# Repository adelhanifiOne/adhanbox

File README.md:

# AdhanBox

AdhanBox est un système automatisé de diffusion de l'adhan (appel à la prière) basé sur ESP32.

## Caractéristiques

- 🕌 **Calcul automatique** des horaires de prière basé sur la géolocalisation
- 🔊 **DFPlayer Mini** pour la lecture audio
- 💡 **Bande LED adressable** SK6812/WS2812 (150 LEDs RGB+W)
- 🌐 **Interface Web** de configuration via point d'accès WiFi
- ⏰ **Horloge RTC DS3231** pour le timing précis
- 📍 **Géolocalisation** WiFi (API HERE) ou manuelle

## Séquence de lecture

- **Fajr** : Piste 2 (0002.mp3) + Duaa (0003.mp3)
- **Autres prières** : Piste 1 (0001.mp3) + Duaa (0003.mp3)

## Matériel requis

- ESP32 (240MHz)
- DS3231 RTC avec batterie
- DFPlayer Mini + carte microSD
- Bande LED SK6812/WS2812 (150 LEDs)
- Haut-parleur/amplificateur
- Bouton de configuration

## Brochage

| Composant | Pin ESP32 |
|-----------|-----------|
| LED Data  | GPIO 13   |
| RTC SDA   | GPIO 5    |
| RTC SCL   | GPIO 4    |
| RTC INT   | GPIO 7    |
| DFPlayer RX | GPIO 2  |
| DFPlayer TX | GPIO 1  |
| Bouton Config | GPIO 11 |

## Installation

1. Installer Arduino IDE ou PlatformIO
2. Installer les bibliothèques :
   - RTClib
   - DFRobotDFPlayerMini
   - Preferences (incluse ESP32)
3. Préparer carte SD avec fichiers audio :
   - `0001.mp3` : Adhan standard
   - `0002.mp3` : Adhan Fajr
   - `0003.mp3` : Duaa
4. Téléverser le sketch sur ESP32

## Configuration

1. Au démarrage, l'ESP32 crée un point d'accès WiFi `AdhanBox-XXXX`
2. Se connecter avec smartphone/PC
3. Accéder à l'interface web (redirection automatique)
4. Configurer :
   - Position géographique
   - Fuseau horaire
   - WiFi (optionnel, pour sync NTP)
   - Volume et luminosité

## Interface Web

- **Tableau** : Vue d'ensemble, contrôles rapides
- **Localisation** : Configuration manuelle ou auto (WiFi)
- **Horaires** : Visualisation des heures de prière
- **Avancé** : RTC, LED, diagnostics

## Scènes lumineuses

- Off / Couleurs statiques (Rouge, Rose, Bleu, Violet, Vert, Jaune)
- Dynamic hue : Cycle de couleurs
- Dynamic fade : Transitions douces
- Luminosité réglable 0-100%

## Licence

Tous droits réservés © 2026 Adel Hanifi. Le dépôt est consultable, mais aucune licence n'est accordée : toute reproduction, modification, distribution ou fabrication demande une autorisation écrite. Voir [LICENSE](LICENSE).

## Auteur

Développé pour la communauté musulmane 🤲

---
**Version:** 1.3.0

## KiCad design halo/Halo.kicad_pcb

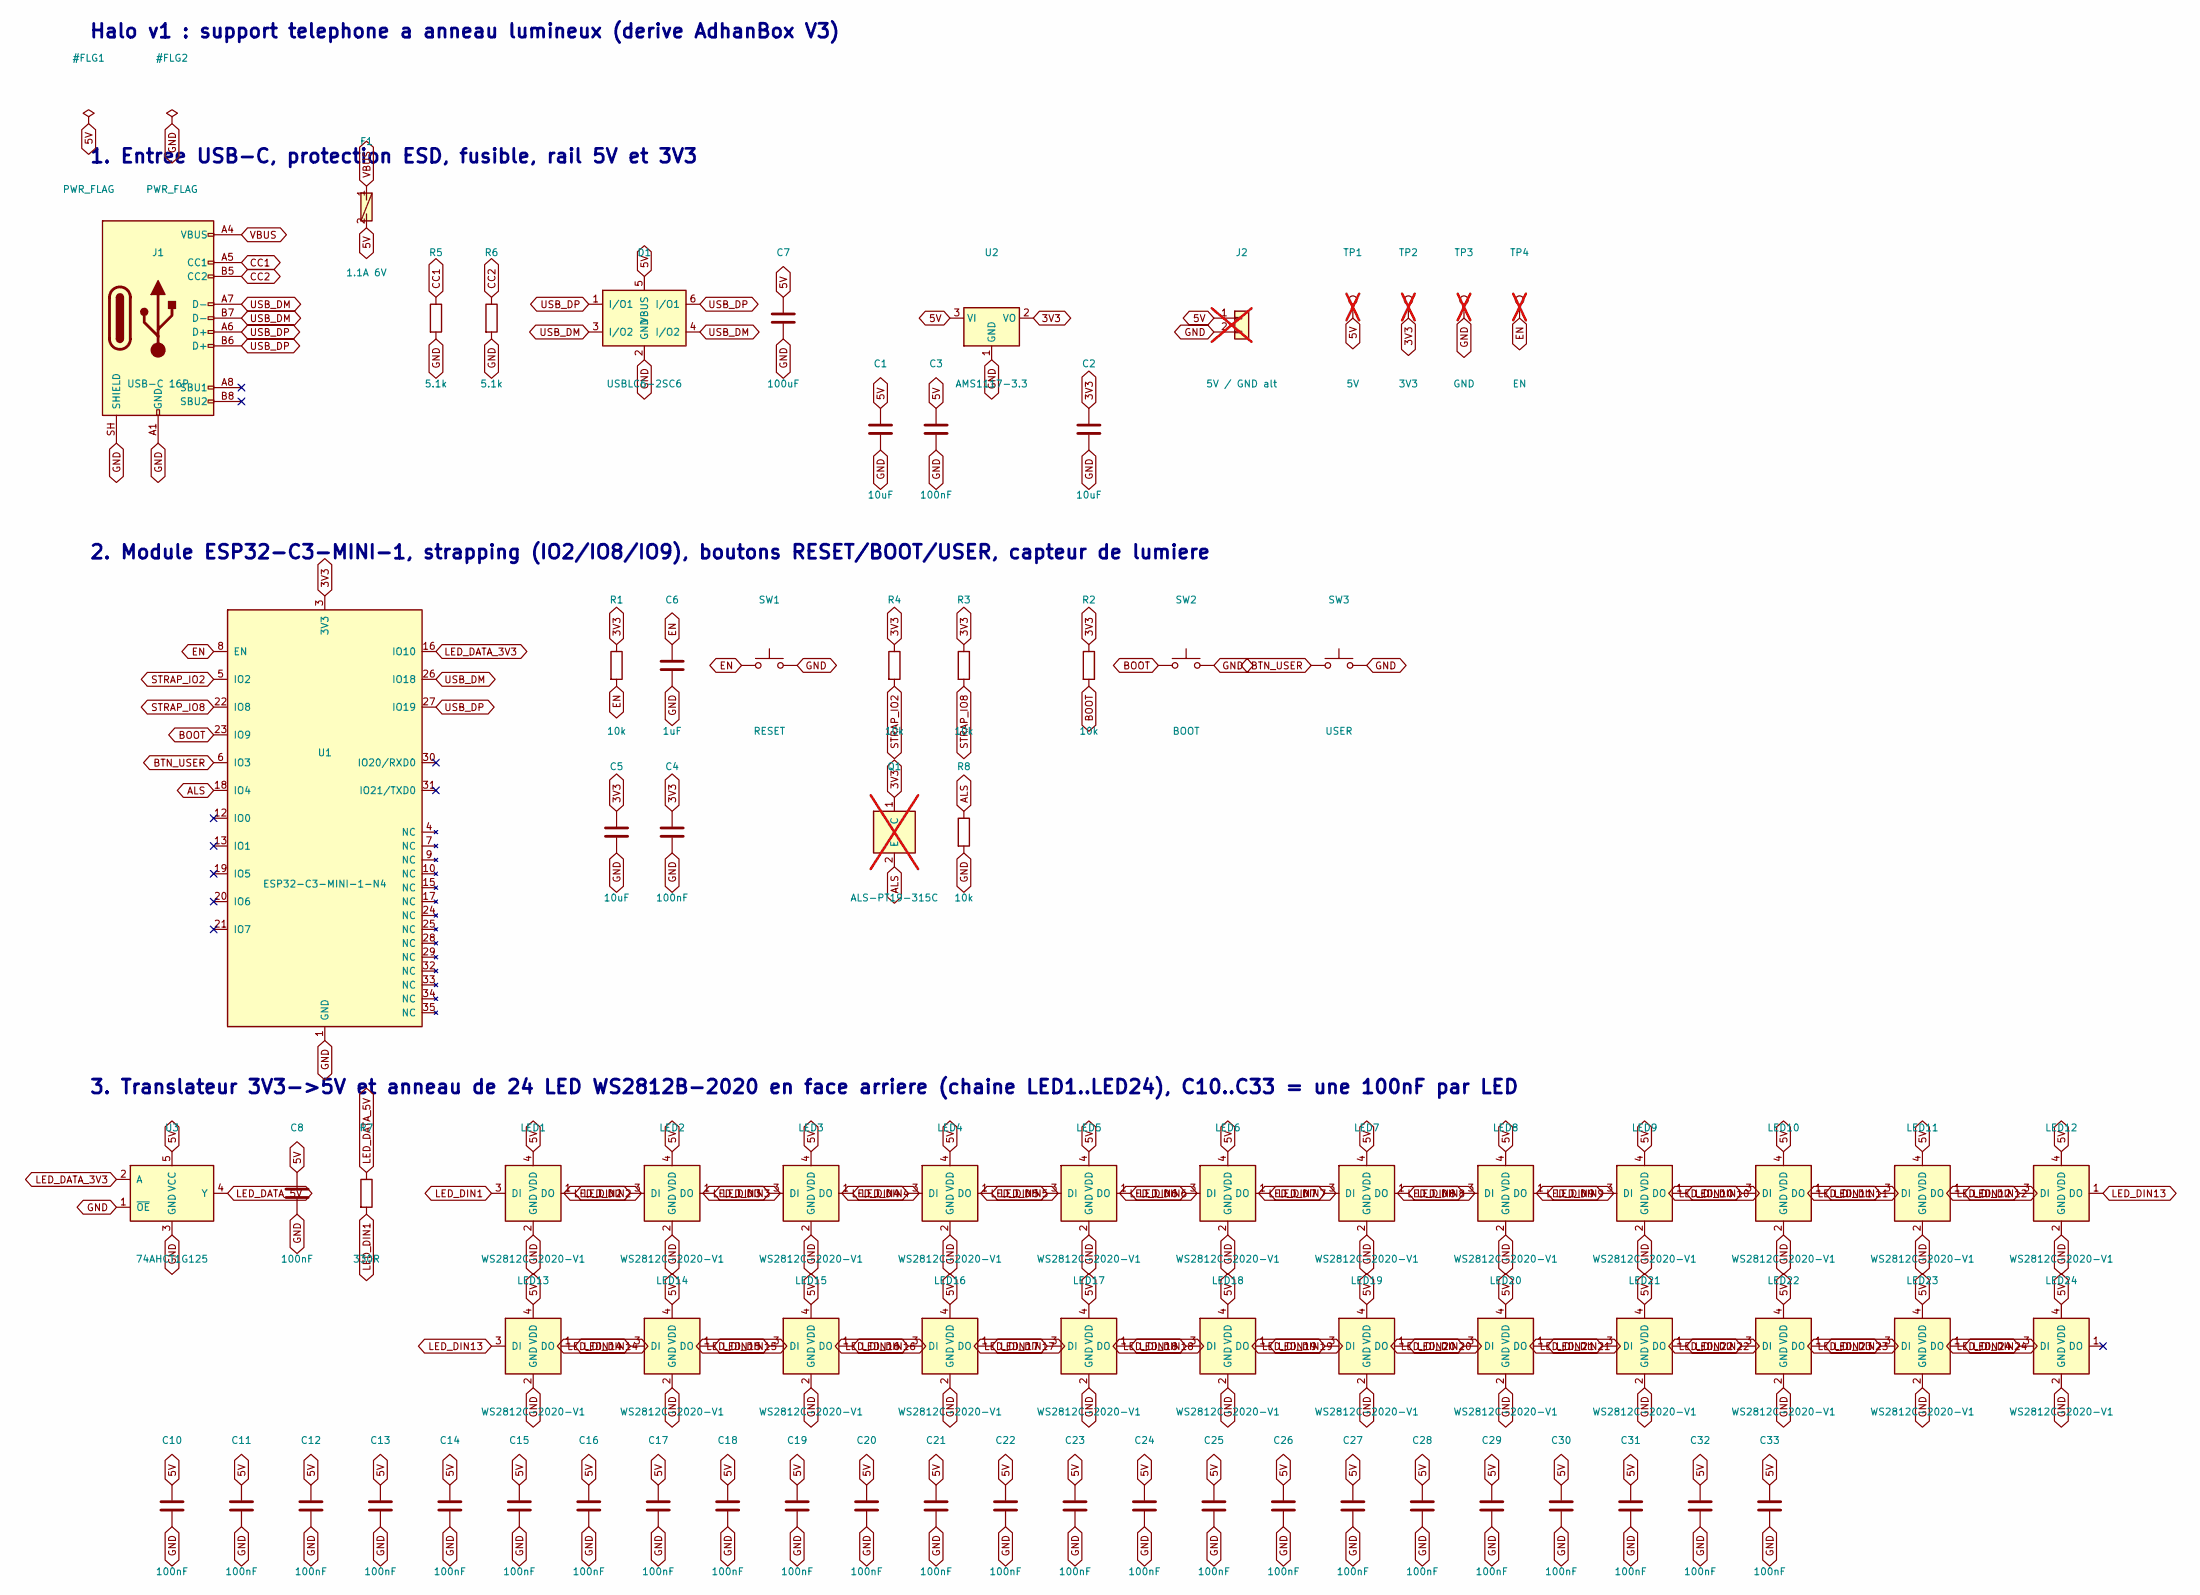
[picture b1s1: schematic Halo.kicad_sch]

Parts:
C1, C2, C5: 10uF; C_0805_2012Metric
C3, C4, C8: 100nF; C_0805_2012Metric
C6: 1uF; C_0805_2012Metric
C7: 100uF; CP_Elec_6.3x5.4
C10, C11, C12, C13, C14, C15, C16, C17, C18, C19, C20, C21, C22, C23, C24, C25, C26, C27, C28, C29, C30, C31, C32, C33: 100nF; C_0603_1608Metric
D1: USBLC6-2SC6; SOT-23-6
F1: 1.1A 6V; Fuse_1206_3216Metric
J1: USB-C 16P; USB_C_Receptacle_HRO_TYPE-C-31-M-12
J2: 5V / GND alt; PinHeader_1x02_P2.54mm_Vertical; not fitted
LED1, LED2, LED3, LED4, LED5, LED6, LED7, LED8, LED9, LED10, LED11, LED12, LED13, LED14, LED15, LED16, LED17, LED18, LED19, LED20, LED21, LED22, LED23, LED24: WS2812C-2020-V1; LED_WS2812B-2020_PLCC4_2.0x2.0mm
Q1: ALS-PT19-315C; LED_0805_2012Metric; not fitted
R1, R2, R3, R4, R8: 10k; R_0805_2012Metric
R5, R6: 5.1k; R_0805_2012Metric
R7: 330R; R_0805_2012Metric
SW1: RESET; SW_SPST_TL3342
SW2: BOOT; SW_SPST_TL3342
SW3: USER; SW_SPST_TL3342
TP1: 5V; TestPoint_Pad_D1.5mm; not fitted
TP2: 3V3; TestPoint_Pad_D1.5mm; not fitted
TP3: GND; TestPoint_Pad_D1.5mm; not fitted
TP4: EN; TestPoint_Pad_D1.5mm; not fitted
U1: ESP32-C3-MINI-1-N4; ESP32-C3-MINI-1
U2: AMS1117-3.3; SOT-223-3_TabPin2
U3: 74AHCT1G125; SOT-23-5

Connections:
3V3: C2.1, C4.1, C5.1, Q1.1 (C), R1.1, R2.1, R3.1, R4.1, TP2.1, U1.3 (3V3), U2.2 (VO)
5V: C1.1, C3.1, C7.1, C8.1, C10.1, C11.1, C12.1, C13.1, C14.1, C15.1, C16.1, C17.1, C18.1, C19.1, C20.1, C21.1, C22.1, C23.1, C24.1, C25.1, C26.1, C27.1, C28.1, C29.1, C30.1, C31.1, C32.1, C33.1, D1.5 (VBUS), F1.2, J2.1, LED1.4 (VDD), LED2.4 (VDD), LED3.4 (VDD), LED4.4 (VDD), LED5.4 (VDD), LED6.4 (VDD), LED7.4 (VDD), LED8.4 (VDD), LED9.4 (VDD), LED10.4 (VDD), LED11.4 (VDD), LED12.4 (VDD), LED13.4 (VDD), LED14.4 (VDD), LED15.4 (VDD), LED16.4 (VDD), LED17.4 (VDD), LED18.4 (VDD), LED19.4 (VDD), LED20.4 (VDD), LED21.4 (VDD), LED22.4 (VDD), LED23.4 (VDD), LED24.4 (VDD), TP1.1, U2.3 (VI), U3.5 (VCC)
ALS: Q1.2 (E), R8.1, U1.18 (IO4)
BOOT: R2.2, SW2.1, U1.23 (IO9)
BTN_USER: SW3.1, U1.6 (IO3)
CC1: J1.A5 (CC1), R5.1
CC2: J1.B5 (CC2), R6.1
EN: C6.1, R1.2, SW1.1, TP4.1, U1.8 (EN)
GND: C1.2, C2.2, C3.2, C4.2, C5.2, C6.2, C7.2, C8.2, C10.2, C11.2, C12.2, C13.2, C14.2, C15.2, C16.2, C17.2, C18.2, C19.2, C20.2, C21.2, C22.2, C23.2, C24.2, C25.2, C26.2, C27.2, C28.2, C29.2, C30.2, C31.2, C32.2, C33.2, D1.2 (GND), J1.A1 (GND), J1.A12 (GND), J1.B1 (GND), J1.B12 (GND), J1.SH (SHIELD), J2.2, LED1.2 (GND), LED2.2 (GND), LED3.2 (GND), LED4.2 (GND), LED5.2 (GND), LED6.2 (GND), LED7.2 (GND), LED8.2 (GND), LED9.2 (GND), LED10.2 (GND), LED11.2 (GND), LED12.2 (GND), LED13.2 (GND), LED14.2 (GND), LED15.2 (GND), LED16.2 (GND), LED17.2 (GND), LED18.2 (GND), LED19.2 (GND), LED20.2 (GND), LED21.2 (GND), LED22.2 (GND), LED23.2 (GND), LED24.2 (GND), R5.2, R6.2, R8.2, SW1.2, SW2.2, SW3.2, TP3.1, U1.1 (GND), U1.2 (GND), U1.11 (GND), U1.14 (GND), U1.36 (GND), U1.37 (GND), U1.38 (GND), U1.39 (GND), U1.40 (GND), U1.41 (GND), U1.42 (GND), U1.43 (GND), U1.44 (GND), U1.45 (GND), U1.46 (GND), U1.47 (GND), U1.48 (GND), U1.49 (GND), U1.50 (GND), U1.51 (GND), U1.52 (GND), U1.53 (GND), U2.1 (GND), U3.1 (~OE), U3.3 (GND)
LED_DATA_3V3: U1.16 (IO10), U3.2 (A)
LED_DATA_5V: R7.1, U3.4 (Y)
LED_DIN1: LED1.3 (DI), R7.2
LED_DIN2: LED1.1 (DO), LED2.3 (DI)
LED_DIN3: LED2.1 (DO), LED3.3 (DI)
LED_DIN4: LED3.1 (DO), LED4.3 (DI)
LED_DIN5: LED4.1 (DO), LED5.3 (DI)
LED_DIN6: LED5.1 (DO), LED6.3 (DI)
LED_DIN7: LED6.1 (DO), LED7.3 (DI)
LED_DIN8: LED7.1 (DO), LED8.3 (DI)
LED_DIN9: LED8.1 (DO), LED9.3 (DI)
LED_DIN10: LED9.1 (DO), LED10.3 (DI)
LED_DIN11: LED10.1 (DO), LED11.3 (DI)
LED_DIN12: LED11.1 (DO), LED12.3 (DI)
LED_DIN13: LED12.1 (DO), LED13.3 (DI)
LED_DIN14: LED13.1 (DO), LED14.3 (DI)
LED_DIN15: LED14.1 (DO), LED15.3 (DI)
LED_DIN16: LED15.1 (DO), LED16.3 (DI)
LED_DIN17: LED16.1 (DO), LED17.3 (DI)
LED_DIN18: LED17.1 (DO), LED18.3 (DI)
LED_DIN19: LED18.1 (DO), LED19.3 (DI)
LED_DIN20: LED19.1 (DO), LED20.3 (DI)
LED_DIN21: LED20.1 (DO), LED21.3 (DI)
LED_DIN22: LED21.1 (DO), LED22.3 (DI)
LED_DIN23: LED22.1 (DO), LED23.3 (DI)
LED_DIN24: LED23.1 (DO), LED24.3 (DI)
STRAP_IO2: R4.2, U1.5 (IO2)
STRAP_IO8: R3.2, U1.22 (IO8)
USB_DM: D1.3 (I/O2), D1.4 (I/O2), J1.A7 (D-), J1.B7 (D-), U1.26 (IO18)
USB_DP: D1.1 (I/O1), D1.6 (I/O1), J1.A6 (D+), J1.B6 (D+), U1.27 (IO19)
VBUS: F1.1, J1.A4 (VBUS), J1.A9 (VBUS), J1.B4 (VBUS), J1.B9 (VBUS)

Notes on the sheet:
Halo v1 : support telephone a anneau lumineux (derive AdhanBox V3)
1. Entree USB-C, protection ESD, fusible, rail 5V et 3V3
2. Module ESP32-C3-MINI-1, strapping (IO2/IO8/IO9), boutons RESET/BOOT/USER, capteur de lumiere
3. Translateur 3V3->5V et anneau de 24 LED WS2812B-2020 en face arriere (chaine LED1..LED24), C10..C33 = une 100nF par LED

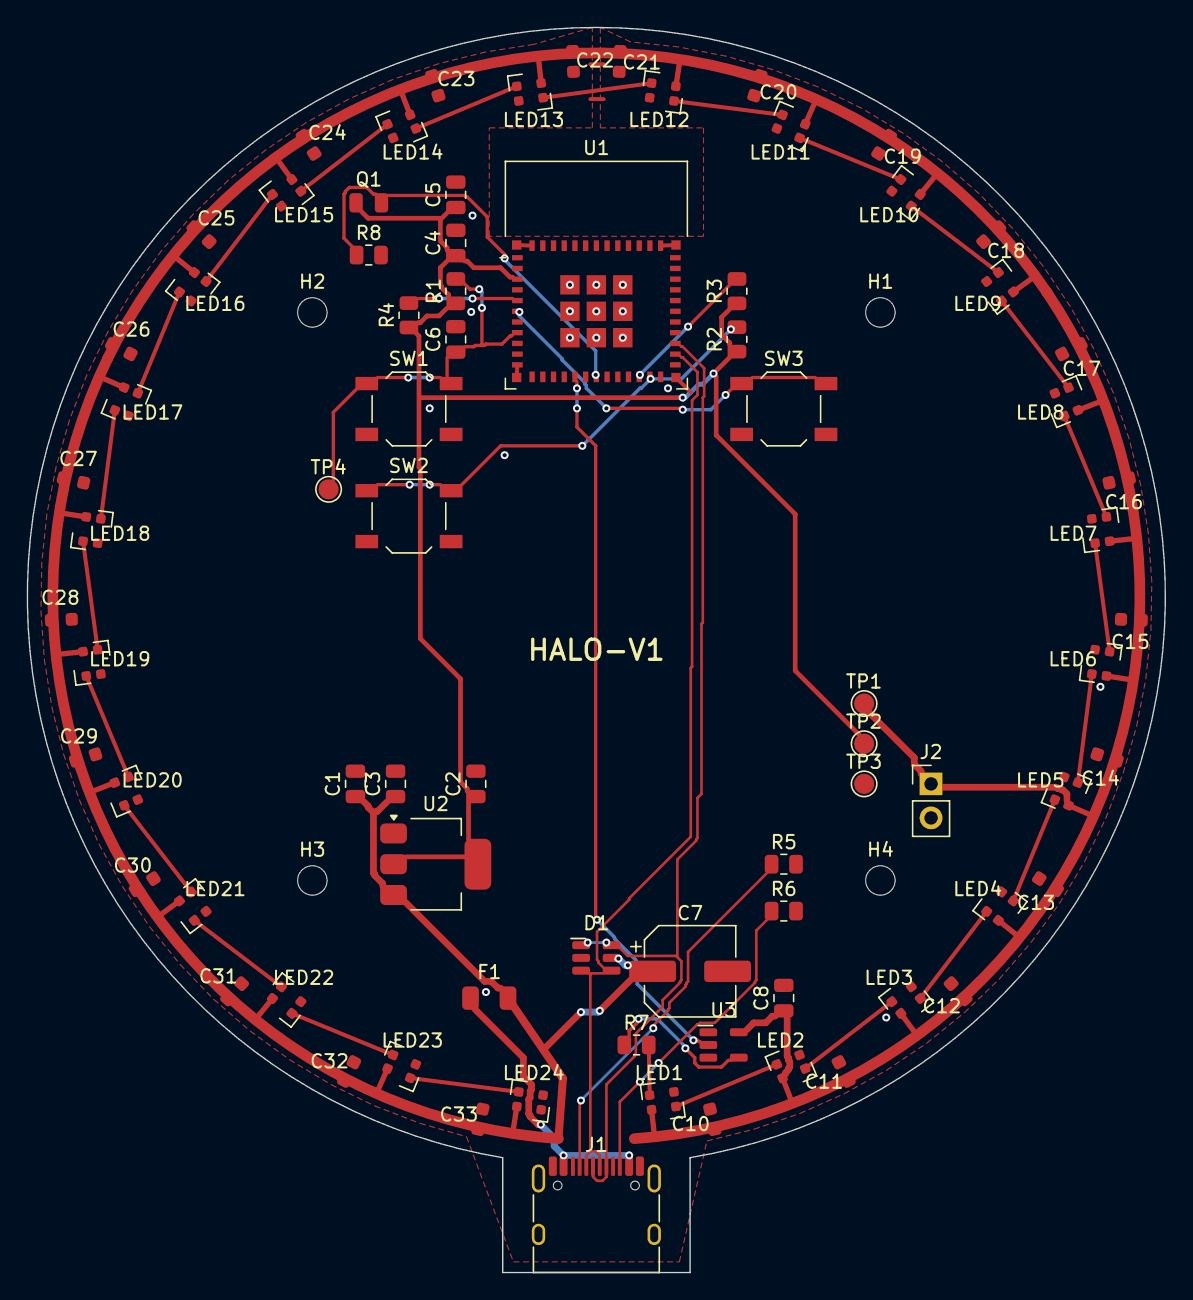
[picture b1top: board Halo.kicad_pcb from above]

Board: 2 copper layers, 85.0 x 93.0 mm, 83 parts (0 on the bottom side), 40 nets.

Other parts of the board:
H1, H2, H3, H4: MountingHole_2.2mm_M2

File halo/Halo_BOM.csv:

Comment,Designator,Footprint,Quantity,LCSC Part #,Note
ESP32-C3-MINI-1-N4,U1,Halo:ESP32-C3-MINI-1,1,C2838111,"module pre-certifie RED, USB natif (pas de CP2102), antenne PCB integree : bord de carte + keep-out 15 mm ; A CONFIRMER sur jlcpcb.com/parts"
AMS1117-3.3,U2,Package_TO_SOT_SMD:SOT-223-3_TabPin2,1,C6186,identique V3
74AHCT1G125GV,U3,Package_TO_SOT_SMD:SOT-23-5,1,C52140417,"translateur 3V3 -> 5V pour la data WS2812 ; MDD, SOT-23-5L, stock JLCPCB 5183 au 09/09/2026"
USBLC6-2SC6,D1,Package_TO_SOT_SMD:SOT-23-6,1,C7519,protection ESD D+/D- ; A CONFIRMER
SMD1206P110TF,F1,Fuse:Fuse_1206_3216Metric,1,C20801,"PTC rearmable RUILON 1206, maintien 1.1 A, coupure 6 V ; le MF-MSMF110-2 de Bourns (C89647) est en boitier 1812, il ne rentre pas dans l empreinte"
USB-C 16P HRO TYPE-C-31-M-12,J1,USB_C_Receptacle_HRO_TYPE-C-31-M-12,1,C165948,"identique V3, sortie vers le bas dans le pied"
Tact switch TL3342,"SW1,SW2,SW3",SW_SPST_TL3342,3,C318884,RESET + BOOT + bouton utilisateur (snooze / scene) ; identique V3
10k 1%,"R1,R2,R3,R4,R8",R_0805_2012Metric,5,C17414,pullups EN / IO9 / IO8 / IO2 + charge capteur lumiere
5.1k 1%,"R5,R6",R_0805_2012Metric,2,C27834,"CC1/CC2 USB-C sink, identique V3"
330R 1%,R7,R_0805_2012Metric,1,C17630,"serie sur la data LED, au plus pres de U3 ; A CONFIRMER"
10uF 25V,"C1,C2,C5",C_0805_2012Metric,3,C15850,entree LDO / sortie LDO / VDD module
100nF 50V X7R,"C3,C4,C8",C_0805_2012Metric,3,C49678,LDO / module / U3
1uF 25V,C6,C_0805_2012Metric,1,C28323,"RC du EN, identique V3"
100uF 16V alu D6.3x5.4,C7,CP_Elec_6.3x5.4,1,C99838,"reservoir rail 5V LED, pres de J1"
100nF 50V X7R,C10-C33,Capacitor_SMD:C_0603_1608Metric,24,C14663,"une par LED, entre VDD et GND de chaque LED"
WS2812C-2020-V1,LED1-LED24,Halo:LED_WS2812B-2020_PLCC4_2.0x2.0mm,24,C2976072,"remplace le WS2812B-2020 (C965555) arrete par Worldsemi et a 4 en stock ; meme boitier 2.2 x 2.0, meme empreinte, meme brochage 1 DO 2 GND 3 DI 4 VDD ; 5 mA par canal au lieu de 12, donc un halo moins lumineux mais un budget USB plus large"
DNP - ALS-PT19-315C/L177/TR8,Q1,LED_SMD:LED_0805_2012Metric,0,,phototransistor lumiere ambiante pour mode nuit auto ; a poser en v1 seulement si valide sur proto ; chercher 'ALS-PT19' sur jlcpcb.com/parts
DNP - pads fils,J2,PinHeader_1x02_P2.54mm_Vertical,0,,2 trous nus 5V/GND : alim alternative si un jour on integre le halo dans un autre boitier
DNP - test points,TP1-TP4,TestPoint_Pad_D1.5mm,0,,pads nus : 5V / 3V3 / GND / EN

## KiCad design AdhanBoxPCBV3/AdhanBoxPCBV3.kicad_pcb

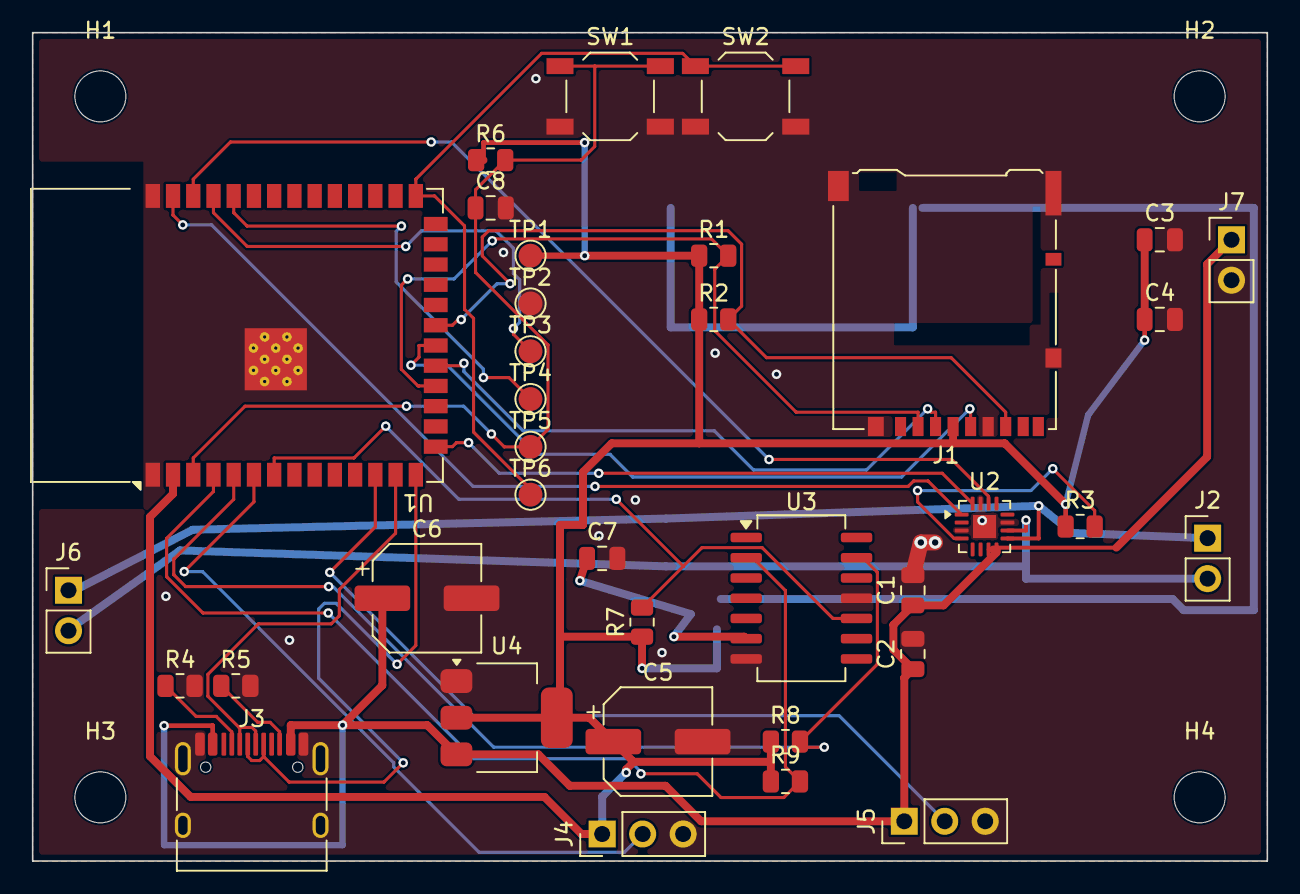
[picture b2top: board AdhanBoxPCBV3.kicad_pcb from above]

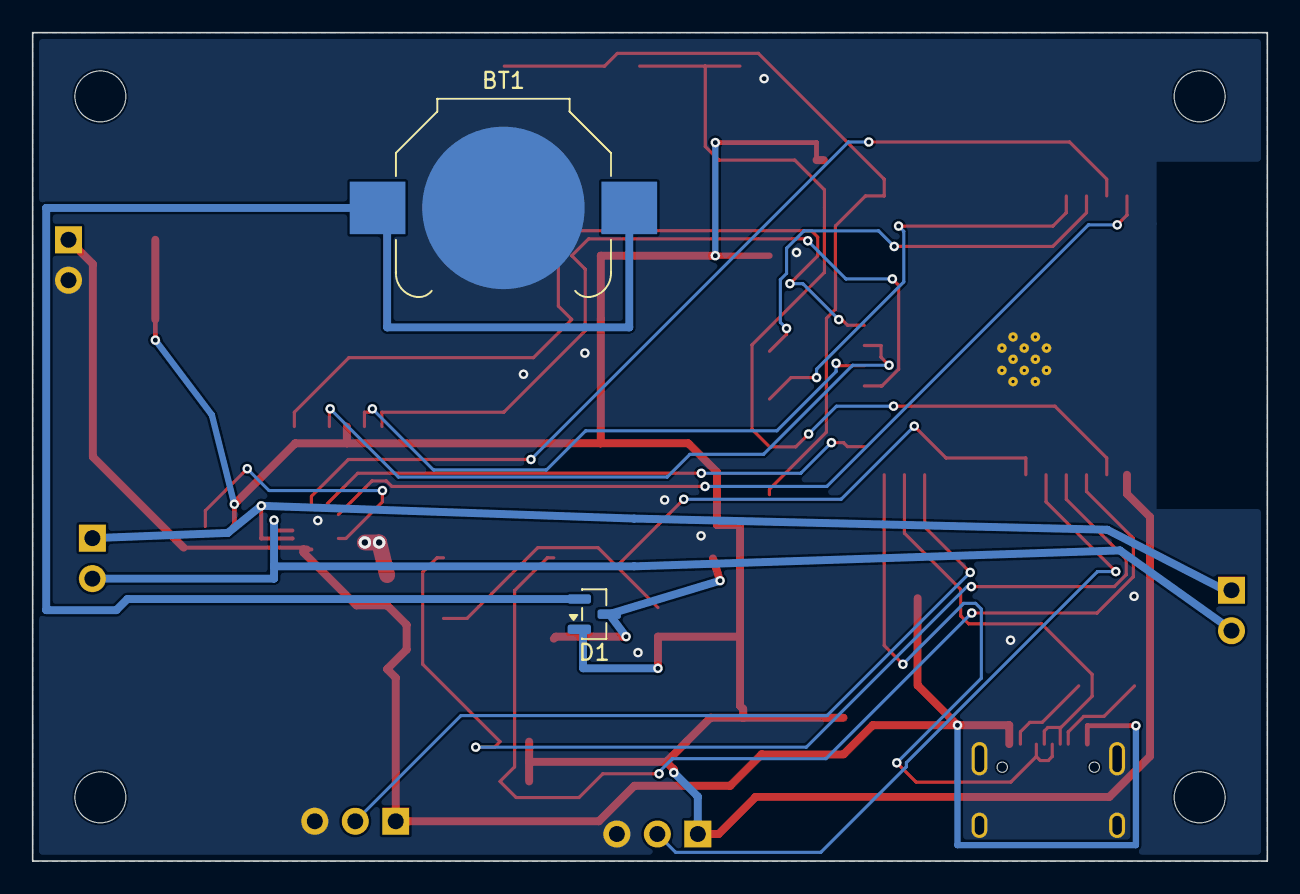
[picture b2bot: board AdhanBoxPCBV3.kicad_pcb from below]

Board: 2 copper layers, 77.5 x 52.0 mm, 42 parts (2 on the bottom side), 28 nets.

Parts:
BT1: CR1225; BatteryHolder_Keystone_3000_1x12mm
C1, C2, C3, C4, C7, C8: C_0805_2012Metric
C5, C6: CP_Elec_6.3x5.4
D1: BAT54C; SOT-23
H1, H2, H3, H4: MountingHole_3.2mm_M3
J1: microSD_HC_Hirose_DM3AT-SF-PEJM5
J2, J6, J7: PinHeader_1x02_P2.54mm_Vertical
J3: USB_C_Receptacle_HRO_TYPE-C-31-M-12
J4, J5: PinHeader_1x03_P2.54mm_Vertical
R1, R2, R3, R4, R5, R6, R7, R8, R9: R_0805_2012Metric
SW1, SW2: SW_SPST_TL3342
TP1, TP2, TP3, TP4, TP5, TP6: TestPoint_Pad_D1.5mm
U1: ESP32-S3-WROOM-1
U2: QFN-16-1EP_3x3mm_P0.5mm_EP1.45x1.45mm
U3: SO-14_5.3x10.2mm_P1.27mm
U4: SOT-223-3_TabPin2

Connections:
3V3: C3.1, C4.1, C5.1, D1.1, J1.4, J4.1, R1.1, R2.1, R3.1, R6.1, R7.1, R8.1, R9.1, TP1.1, U1.2, U4.2
5V: C1.1, C2.1, C6.1, J3.A4, J3.A9, J3.B4, J3.B9, J5.1, J7.1, U2.7, U2.8, U4.3
AUDIO_BCLK: U1.15, U2.16
AUDIO_DIN: U1.39, U2.1
AUDIO_LRC: U1.38, U2.14
BOOT: SW2.1, TP6.1, U1.27
BTN: J4.2, U1.6
CC1: J3.A5, R4.1
CC2: J3.B5, R5.1
EN: C8.1, R6.2, SW1.1, TP5.1, U1.3
GND: BT1.2, C1.2, C2.2, C3.2, C4.2, C5.2, C6.2, C7.2, C8.2, J1.6, J1.SH, J3.A1, J3.A12, J3.B1, J3.B12, J3.SH, J4.3, J5.3, J7.2, R4.2, R5.2, SW1.2, SW2.2, TP2.1, U1.1, U1.40, U1.41, U2.3, U2.11, U2.15, U2.17, U3.7, U3.11, U4.1
LED_DATA: J5.2, U1.12
MAX_SD: R3.2, U2.4
RTC_BATT: BT1.1, D1.2
RTC_SCL: R9.2, U1.4, U3.2
RTC_SDA: R8.2, U1.5, U3.13
RTC_SQW: R7.2, U1.7, U3.10
RTC_VDD: C7.1, D1.3, U3.6
RX: TP4.1, U1.36
SD_CS: J1.2, R1.2, U1.18
SD_MISO: J1.7, R2.2, U1.21
SD_MOSI: J1.3, U1.19
SD_SCK: J1.5, U1.20
SPK_N: J2.2, J6.2, U2.10
SPK_P: J2.1, J6.1, U2.9
TX: TP3.1, U1.37
USB_DN: J3.A7, J3.B7, U1.13
USB_DP: J3.A6, J3.B6, U1.14

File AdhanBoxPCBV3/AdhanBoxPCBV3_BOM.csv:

Comment,Designator,Footprint,Quantity,LCSC Part #,Note
ESP32-S3-WROOM-1-N4R2,U1,RF_Module:ESP32-S3-WROOM-1,1,C2913203,"module pre-certifie, PSRAM 2MB garanti, pose machine"
MAX98357AETE+T,U2,QFN-16-1EP_3x3mm,1,C910544,
RX8025T-UC Epson (DTCXO ±3.8ppm),U3,SO-14_5.3x10.2mm,1,C53691,"authentique; variante -UB = C17353; AUCUN quartz externe requis"
AMS1117-3.3,U4,SOT-223-3_TabPin2,1,C6186,
USB-C 16P HRO TYPE-C-31-M-12,J3,HRO_TYPE-C-31-M-12,1,C165948,
microSD Hirose DM3AT,J1,DM3AT-SF-PEJM5,1,C114218,"GARDE (qualite): les contacts SD sont le point faible connu, pas d economie ici"
Tact switch TL3342,"SW1,SW2",SW_SPST_TL3342,2,C318884,"RESET + BOOT"
100nF 50V X7R,"C1,C3,C7",C_0805,3,C49678,
10uF 25V,"C2,C4",C_0805,2,C15850,
1uF 25V,C8,C_0805,1,C28323,"RC du EN"
100uF 16V alu D6.3x5.4,"C5,C6",CP_Elec_6.3x5.4,2,C99838,
10k 1%,"R1,R2,R6,R7,R8,R9",R_0805,6,C17414,"pullups SD/EN/INT/I2C"
100k 1%,R3,R_0805,1,C17407,
5.1k 1%,"R4,R5",R_0805,2,C27834,"CC1/CC2 USB-C sink"
DNP - pads fils,"J2,J4,J5,J6,J7",PinHeader tht,0,,"trous nus: J2+J6 = 2 enceintes (8 ohms chacune!), TTP223, LED, 5V alt"
DNP - test points,"TP1-TP6",TestPoint_Pad_D1.5mm,0,,"pads nus: 3V3/GND/TX/RX/EN/IO0"
BAT54C double Schottky cathode commune (JSCJ),D1,SOT-23,1,C2135,"aiguillage 3V3/pile du RTC; FACE ARRIERE avec BT1 (seuls composants au dos)"
Support pile Keystone 3000 (retenue CMS 12mm),BT1,BatteryHolder_Keystone_3000_1x12mm,1,,"FACE ARRIERE. Ref EXACTE Keystone 3000 (DigiKey 36-3000-ND): 2 pattes CMS espacees de 15.8mm, pastille centrale 10.2mm - NE PAS substituer. Accepte CR1216/1220/1225; on utilise CR1225 (~7 ans a 0.75uA), pile fournie dans la boite"

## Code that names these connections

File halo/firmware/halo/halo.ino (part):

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
// ── Brochage ─────────────────────────────────────────────────────────────────
#define LED_NUM       24
#define LED_DATA_PIN  10
#define BTN_PIN       3      // SW3 vers GND
#define ALS_PIN       4      // ALS-PT19 + R8 10k vers GND : 0 V dans le noir

// ── Luminosite ───────────────────────────────────────────────────────────────
// L'app regle 0..100 ; l'anneau ne depasse jamais BRIGHT_CAP % (24 LED d'une
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static unsigned long wifiConnectStart = 0;
#define WIFI_CONNECT_TIMEOUT_MS 20000UL

Adafruit_NeoPixel leds(LED_NUM, LED_DATA_PIN, NEO_GRB + NEO_KHZ800);
WebServer server(80);
Preferences prefs;
DNSServer dnsServer;
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  unsigned long now = millis();
  if (now - lastAls < 500) return;
  lastAls = now;
  int raw = analogRead(ALS_PIN);
  alsEma = (alsEma < 0) ? raw : (alsEma * 0.8f + raw * 0.2f);
  prefs.begin("adhancfg", true);
  bool present = prefs.getBool("als_present", true);
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  static unsigned long downAt = 0;
  static bool longDone = false;
  static unsigned long lastEdge = 0;
  bool down = (digitalRead(BTN_PIN) == LOW);
  unsigned long now = millis();
  if (down != wasDown && now - lastEdge < 40) return;   // anti-rebond
  if (down && !wasDown) { downAt = now; longDone = false; lastEdge = now; }
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    bancRep("{\"hardware\":\"" HALO_HARDWARE "\",\"version\":\"" HALO_VERSION "\",\"device_id\":\"" + deviceIdHex() + "\",\"token\":\"" + _apiToken + "\"}");
  } else if (c == "diag") {
    char buf[200];
    snprintf(buf, sizeof(buf), "{\"free_heap\":%u,\"als\":%d,\"btn\":%d,\"time_ok\":%s,\"wifi\":%s}", (unsigned)ESP.getFreeHeap(), analogRead(ALS_PIN),
             digitalRead(BTN_PIN), timeSet() ? "true" : "false", WiFi.isConnected() ? "true" : "false");
    bancRep(buf);
  } else if (c.startsWith("led")) {
    int sc = c.substring(3).toInt();
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    esp_task_wdt_reconfigure(&wdtCfg);
  }

  pinMode(BTN_PIN, INPUT_PULLUP);
  analogReadResolution(12);
  analogSetPinAttenuation(ALS_PIN, ADC_11db);

  prefs.begin("adhancfg", true);
  ledBrightness = prefs.getInt("brightness", 50);
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    const unsigned long BLE_INACTIVITY_TIMEOUT_MS = 5UL * 60UL * 1000UL;
    unsigned long bleInactivityTimer = millis();
    bool bleHadClient = false;
    bool btnWasUp = (digitalRead(BTN_PIN) == HIGH);
    while (true) {
      unsigned long now = millis();
      _fxBright = effectiveBrightness();
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        if (tcmd.startsWith("t:")) { bancCommande(tcmd.substring(2)); break; }
      }
      // Bouton : sortie manuelle (sauf appairage demande explicitement)
      bool btnUp = (digitalRead(BTN_PIN) == HIGH);
      if (!pairBoot && btnWasUp && !btnUp) {
        delay(80);
        if (digitalRead(BTN_PIN) == LOW) { Serial.println("[BLE] bouton : arret"); break; }
      }
      btnWasUp = btnUp;
      delay(100);
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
